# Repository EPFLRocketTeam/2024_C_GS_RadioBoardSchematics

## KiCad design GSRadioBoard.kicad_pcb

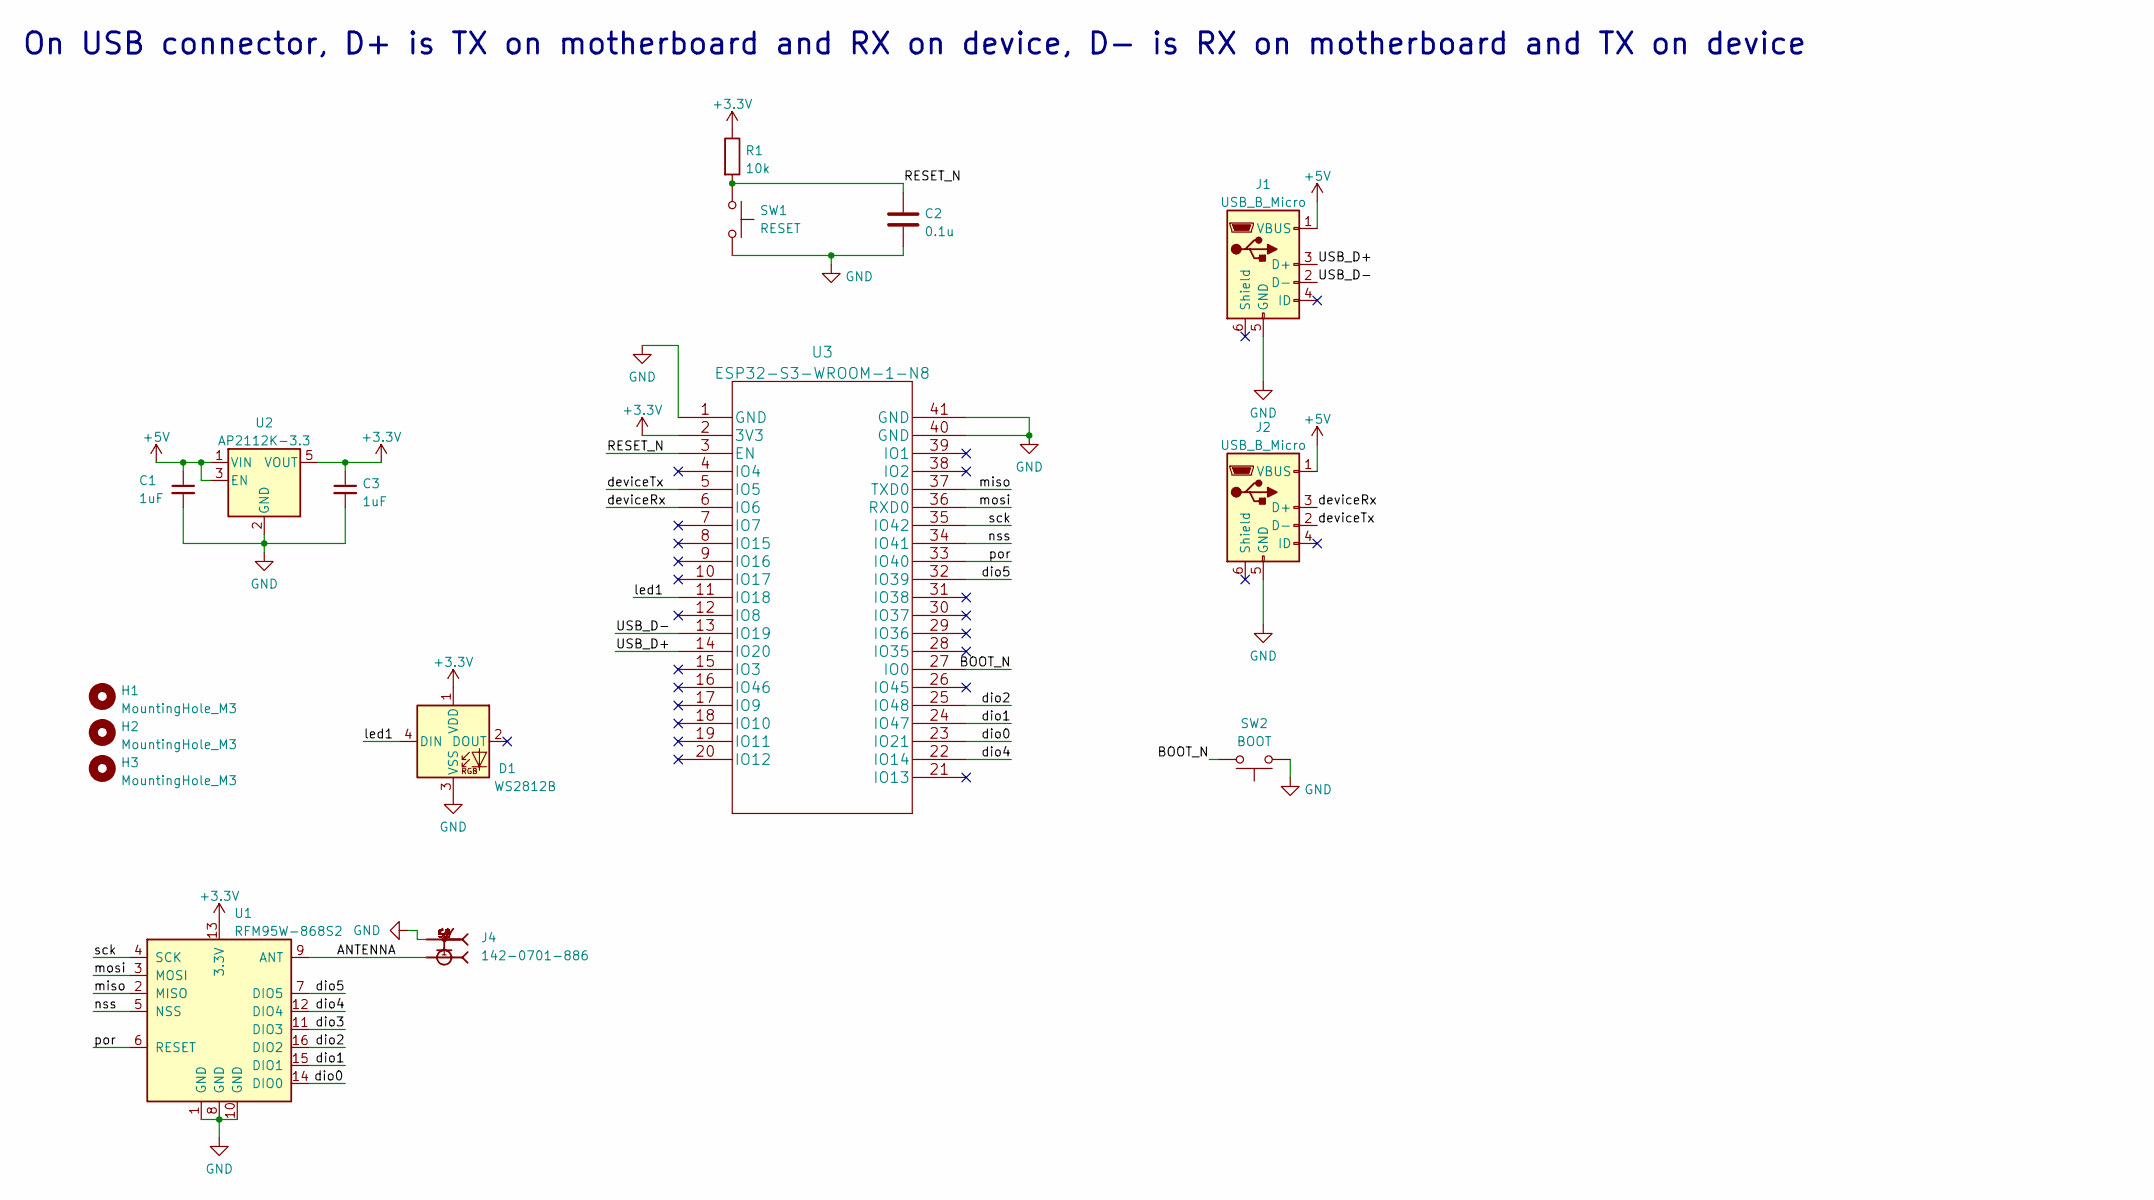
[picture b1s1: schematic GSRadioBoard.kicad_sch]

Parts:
C1, C3: 1uF; C_0603_1608Metric
C2: 0.1u; C_0603_1608Metric
D1: WS2812B; LED_WS2812B_PLCC4_5.0x5.0mm_P3.2mm
H1, H2, H3: MountingHole_M3; MountingHole_3.2mm_M3
J1, J2: USB_B_Micro; USB_Micro-B_Wuerth_629105150521
J4: 142-0701-886; TAOGLAS_EMPCB.SMAFSTJ.B.HT; PARTREV 4a
R1: 10k; R_0603_1608Metric
SW1: RESET; PTS815 SJK 250 SMTR LFS
SW2: BOOT; PTS815 SJK 250 SMTR LFS
U1: RFM95W-868S2; HOPERF_RFM9XW_SMD
U2: AP2112K-3.3; SOT-23-5
U3: ESP32-S3-WROOM-1-N8; ESP32-S3-WROOM-1

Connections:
+3.3V: C3.1, D1.1 (VDD), R1.1, U2.5 (VOUT), U3.2 (3V3); also elsewhere on the board
+5V: C1.1, J1.1 (VBUS), J2.1 (VBUS), U2.1 (VIN), U2.3 (EN)
/ANTENNA: J4.1; also elsewhere on the board
/BOOT_N: SW2.2, U3.27 (IO0)
/RESET_N: C2.1, R1.2, SW1.1, U3.3 (EN)
/USB_D+: J1.3 (D+), U3.14 (IO20)
/USB_D-: J1.2 (D-), U3.13 (IO19)
/deviceRx: J2.3 (D+), U3.6 (IO6)
/deviceTx: J2.2 (D-), U3.5 (IO5)
/dio0: U3.23 (IO21); also elsewhere on the board
/dio1: U3.24 (IO47); also elsewhere on the board
/dio2: U3.25 (IO48); also elsewhere on the board
/dio4: U3.22 (IO14); also elsewhere on the board
/dio5: U3.32 (IO39); also elsewhere on the board
/led1: D1.4 (DIN), U3.11 (IO18)
/miso: U3.37 (TXD0); also elsewhere on the board
/mosi: U3.36 (RXD0); also elsewhere on the board
/nss: U3.34 (IO41); also elsewhere on the board
/por: U3.33 (IO40); also elsewhere on the board
/sck: U3.35 (IO42); also elsewhere on the board
GND: C1.2, C2.2, C3.2, D1.3 (VSS), J1.5 (GND), J2.5 (GND), J4.S1, J4.S2, J4.S3, J4.S4, SW1.2, SW2.1, U2.2 (GND), U3.1 (GND), U3.40 (GND), U3.41 (GND); also elsewhere on the board

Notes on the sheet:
On USB connector, D+ is TX on motherboard and RX on device, D- is RX on motherboard and TX on device

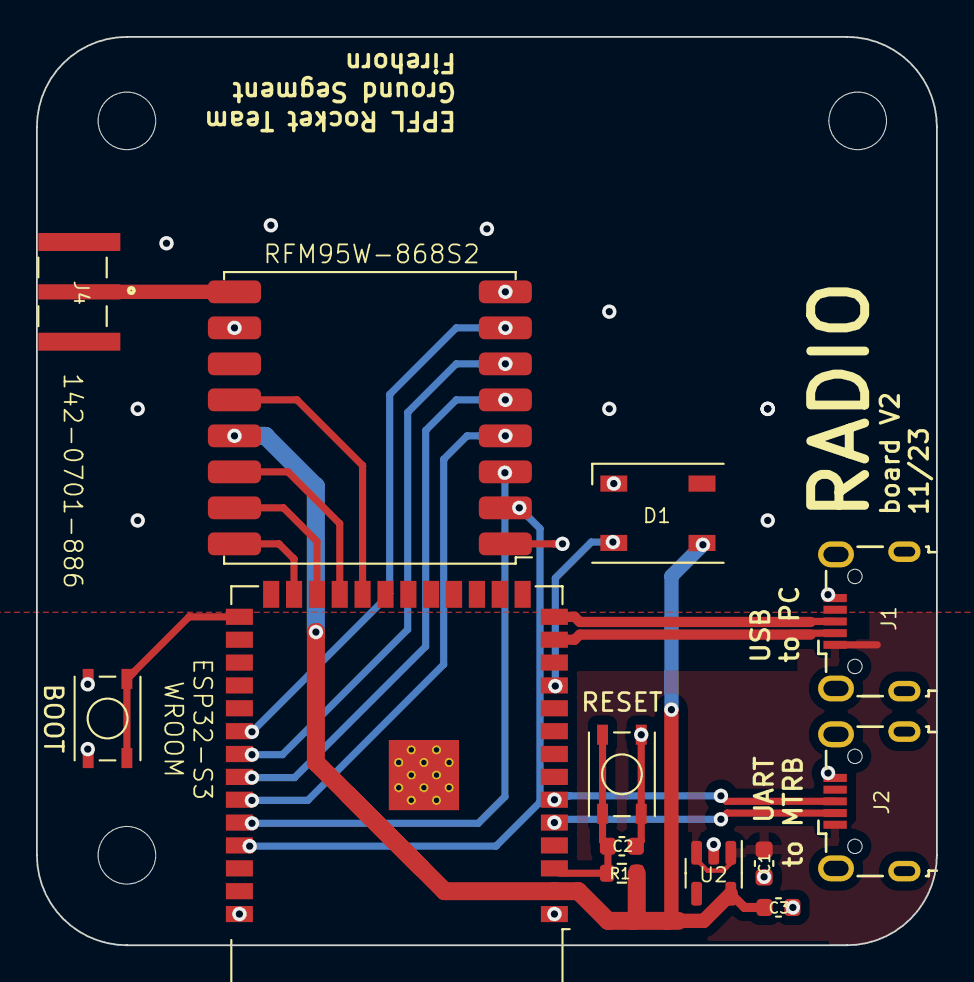
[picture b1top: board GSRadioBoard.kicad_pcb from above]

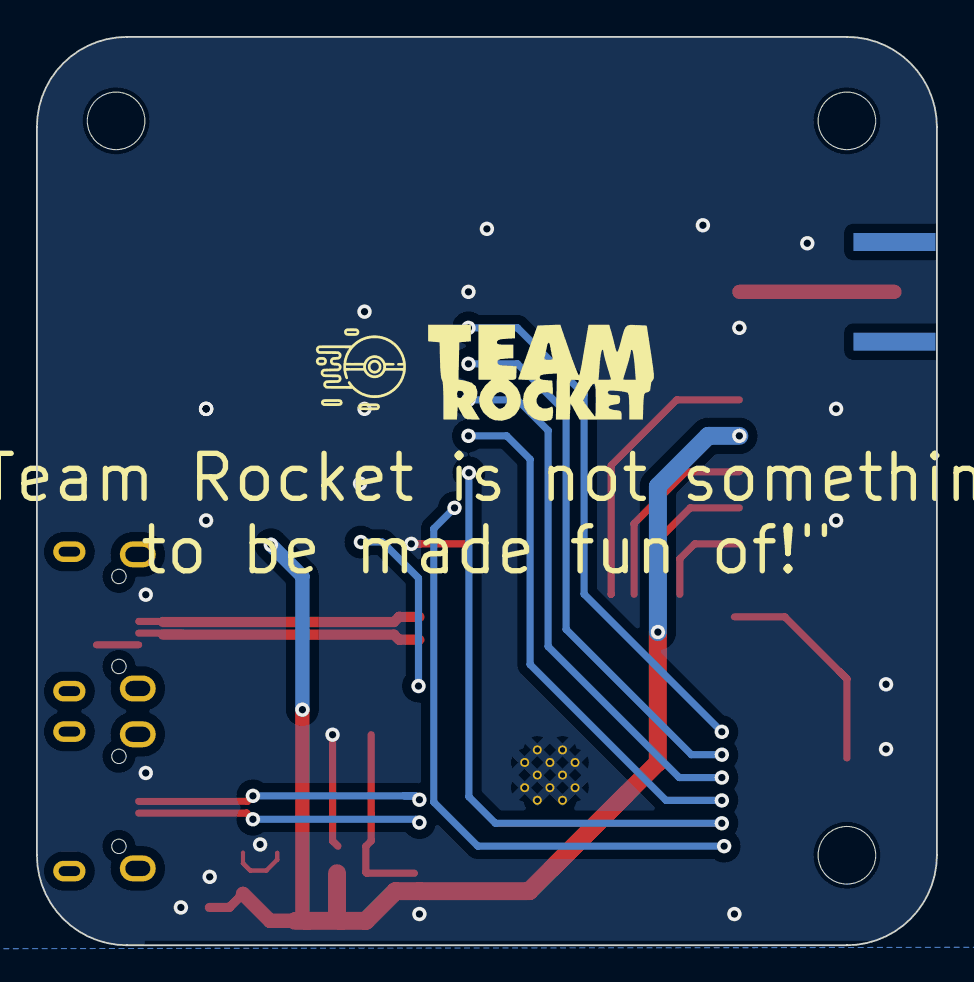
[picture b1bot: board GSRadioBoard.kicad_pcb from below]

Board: 2 copper layers, 50.0 x 50.5 mm, 18 parts (2 on the bottom side), 21 nets.

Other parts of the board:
Pokeball: LOGO; pokeball
TeamRocket: LOGO; teamrocket
U4: RFM95W-868S2; HOPERF_RFM9XW_SMD

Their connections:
+3.3V: U4.13 (3.3V); also elsewhere on the board
/ANTENNA: U4.9 (ANT); also elsewhere on the board
/dio0: U4.14 (DIO0); also elsewhere on the board
/dio1: U4.15 (DIO1); also elsewhere on the board
/dio2: U4.16 (DIO2); also elsewhere on the board
/dio4: U4.12 (DIO4); also elsewhere on the board
/dio5: U4.7 (DIO5); also elsewhere on the board
/miso: U4.2 (MISO); also elsewhere on the board
/mosi: U4.3 (MOSI); also elsewhere on the board
/nss: U4.5 (NSS); also elsewhere on the board
/por: U4.6 (RESET); also elsewhere on the board
/sck: U4.4 (SCK); also elsewhere on the board
GND: U4.1 (GND), U4.8 (GND), U4.10 (GND); also elsewhere on the board

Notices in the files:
parts and their libraries:
Copyright 2021 Accelerated Designs. All rights reserved.
